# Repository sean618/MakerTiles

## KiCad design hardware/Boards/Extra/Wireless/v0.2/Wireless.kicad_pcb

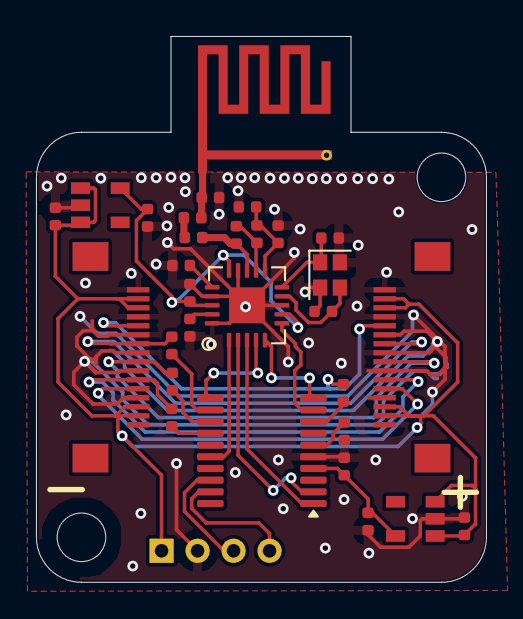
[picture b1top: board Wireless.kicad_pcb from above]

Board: 4 copper layers, 25.0 x 30.3 mm, 34 parts (0 on the bottom side), 31 nets.

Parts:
AE1: Antenna_MIFA_Cypress; Antenna_cypress_MIFA
C1: 0.1uF; C_0402_1005Metric
C2, C8, C9, C11, C12, C13: 4.7uF; C_0402_1005Metric
C3: 33nF; C_0402_1005Metric
C4: 2.2nF; C_0402_1005Metric
C5, C6: 12pF; C_0402_1005Metric
C7: 1pF; C_0402_1005Metric
C10: 1.5pF; C_0402_1005Metric
C14: 4.7pF; C_0402_1005Metric
H1, H2: M2.5MountingHole; MountingHole_2.7mm_M2.5_ISO7380
IGNORE1: Wireless v0.2; BoardText
J1, J3: FFC_connector_16p_hinge_lock
J4: swd_4pin; swd_header
L1: 8.2nH; C_0402_1005Metric
L3: 3.9nH; C_0402_1005Metric
L4: 2.7nH; C_0402_1005Metric
R1, R2, R3, R4: 120R; R_0402_1005Metric
R6: 22K; R_0402_1005Metric
U1, U2: ME6211C33M5G-N; SOT-23-5
U3: STM32G030F6P6; TSSOP-20_4.4x6.5mm_P0.65mm
U4: NRF24L01; QFN-20-1EP_4x4mm_P0.5mm_EP2.5x2.5mm
Y2: Crystal_16M_small; Crystal_SMD_2016-4Pin_2.0x1.6mm

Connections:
5V: C8.1, C11.1, J1.2, J1.3, J1.14, J1.15, J3.2, J3.3, J3.14, J3.15, J4.1, U1.1 (IN), U1.3 (EN), U2.1 (IN), U2.3 (EN)
GND: AE1.2 (GND), C1.2, C2.2, C3.2, C4.2, C5.2, C6.2, C7.2, C8.2, C9.2, C11.2, C12.2, C13.2, C14.2, J1.1, J1.4, J1.6, J1.8, J1.10, J1.13, J1.16, J3.1, J3.4, J3.7, J3.9, J3.11, J3.13, J3.16, J4.2, R6.1, U1.2 (GND), U2.2 (GND), U3.5 (VSS), U4.8 (VSS), U4.14 (VSS), U4.17 (VSS), U4.20 (VSS), U4.21 (VSS), Y2.2 (GND), Y2.4 (GND)
Interrupt/CAN: J1.12, J3.5
MISO: J1.9, J3.8, R4.2
MOSI: J1.11, J3.6, R2.2
unnamed: AE1.1 (A), C7.1, C10.2
unnamed: C10.1, L3.1
unnamed: C1.1, U3.6 (NRST)
unnamed: R1.1, U3.8 (PA1)
unnamed: R3.1, U3.12 (PA5)
unnamed: R4.1, U3.13 (PA6)
unnamed: R2.1, U3.14 (PA7)
unnamed: L1.1, L4.2, U4.12 (ANT1)
unnamed: L1.2, L3.2, U4.13 (ANT2)
unnamed: C3.1, U4.19 (DVDD)
unnamed: R6.2, U4.16 (IREF)
unnamed: C4.1, C14.1, L4.1, U4.11 (VDD_PA)
PS: J1.5, J3.12, R1.2
SCLK: J1.7, J3.10, R3.2
SWDCLK: J4.4, U3.19 (PA14/PA15)
SWDIO: J4.3, U3.18 (PA13)
VDD: C2.1, C12.1, U2.5 (OUT), U3.4 (VDD)
VDD_NRF: C9.1, C13.1, U1.5 (OUT), U4.7 (VDD), U4.15 (VDD), U4.18 (VDD)
W_CSN: U3.2 (PC14/PB9), U4.2 (CSN)
W_Enable: U3.16 (PA11/PA9), U4.1 (CE)
W_INT: U3.9 (PA2), U4.6 (IRQ)
W_MISO: U3.10 (PA3), U4.5 (MISO)
W_MOSI: U3.11 (PA4), U4.4 (MOSI)
W_SCK: U3.1 (PB7/PB8), U4.3 (SCK)
XC13: C5.1, U4.10 (XC1), Y2.1
XC23: C6.1, U4.9 (XC2), Y2.3

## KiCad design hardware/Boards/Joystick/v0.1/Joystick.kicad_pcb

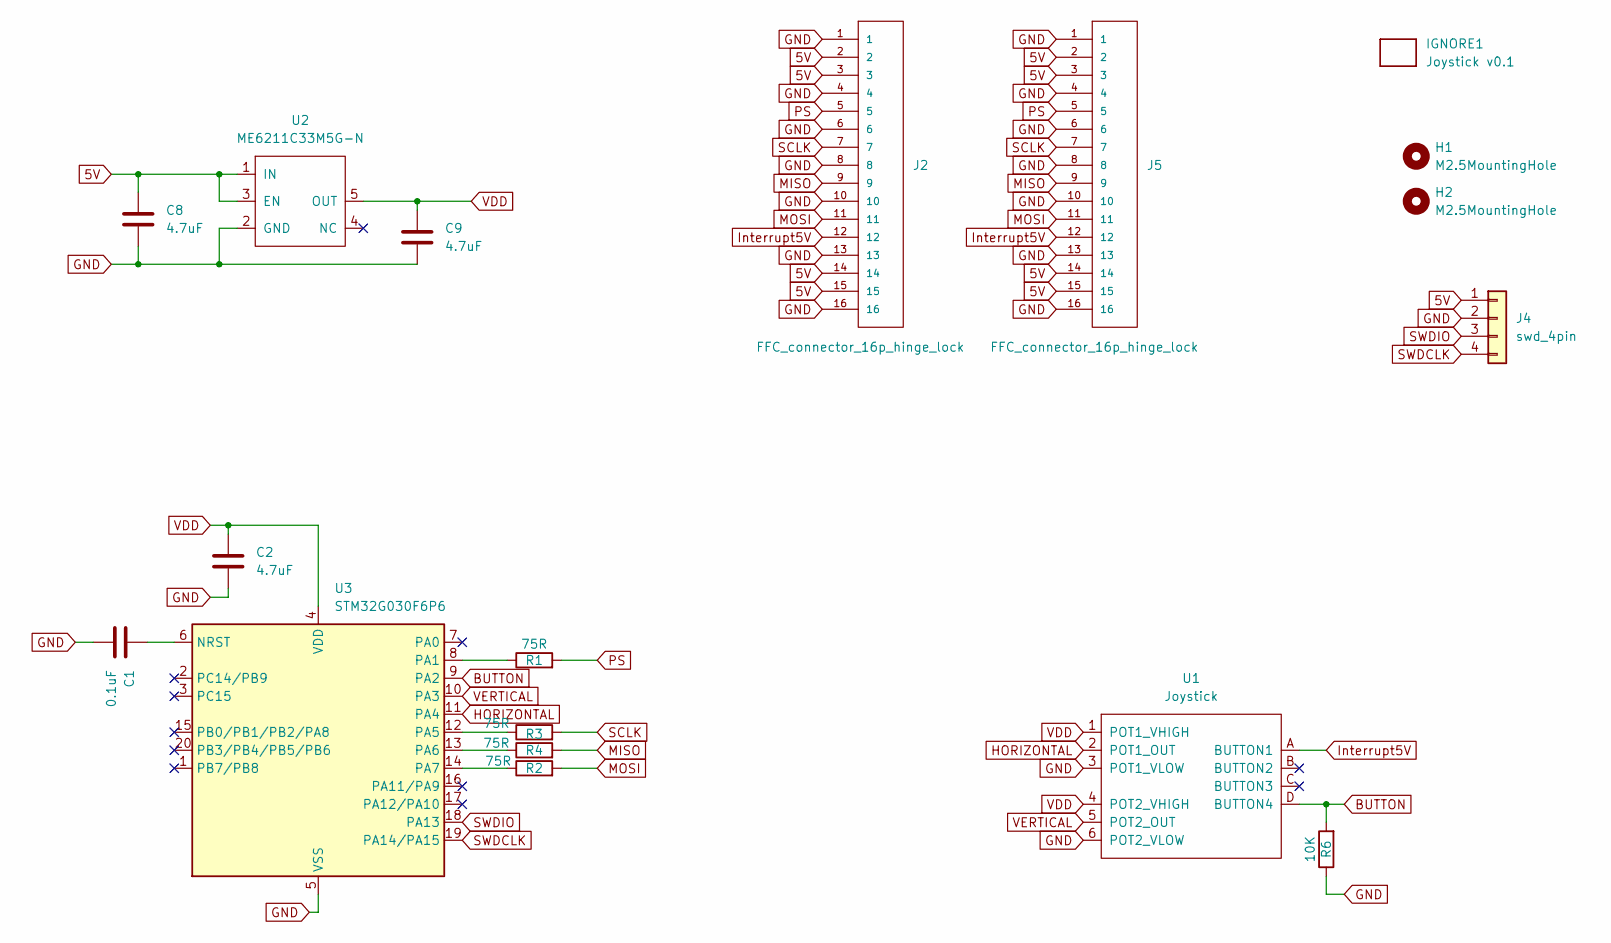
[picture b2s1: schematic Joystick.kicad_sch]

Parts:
C1: 0.1uF; C_0402_1005Metric
C2, C8, C9: 4.7uF; C_0402_1005Metric
H1, H2: M2.5MountingHole; MountingHole_2.7mm_M2.5_ISO7380
IGNORE1: Joystick v0.1; BoardText
J2, J5: FFC_connector_16p_hinge_lock
J4: swd_4pin; swd_header
R1, R2, R3, R4: 75R; R_0402_1005Metric
R6: 10K; R_0402_1005Metric
U1: Joystick
U2: ME6211C33M5G-N; SOT-23-5
U3: STM32G030F6P6; TSSOP-20_4.4x6.5mm_P0.65mm

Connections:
5V: C8.1, J2.2, J2.3, J2.14, J2.15, J4.1, J5.2, J5.3, J5.14, J5.15, U2.1 (IN), U2.3 (EN)
BUTTON: R6.2, U1.D (BUTTON4), U3.9 (PA2)
GND: C1.2, C2.2, C8.2, C9.2, J2.1, J2.4, J2.6, J2.8, J2.10, J2.13, J2.16, J4.2, J5.1, J5.4, J5.6, J5.8, J5.10, J5.13, J5.16, R6.1, U1.3 (POT1_VLOW), U1.6 (POT2_VLOW), U2.2 (GND), U3.5 (VSS)
HORIZONTAL: U1.2 (POT1_OUT), U3.11 (PA4)
Interrupt5V: J2.12, J5.12, U1.A (BUTTON1)
MISO: J2.9, J5.9, R4.2
MOSI: J2.11, J5.11, R2.2
unnamed: C1.1, U3.6 (NRST)
unnamed: R1.1, U3.8 (PA1)
unnamed: R3.1, U3.12 (PA5)
unnamed: R4.1, U3.13 (PA6)
unnamed: R2.1, U3.14 (PA7)
PS: J2.5, J5.5, R1.2
SCLK: J2.7, J5.7, R3.2
SWDCLK: J4.4, U3.19 (PA14/PA15)
SWDIO: J4.3, U3.18 (PA13)
VDD: C2.1, C9.1, U1.1 (POT1_VHIGH), U1.4 (POT2_VHIGH), U2.5 (OUT), U3.4 (VDD)
VERTICAL: U1.5 (POT2_OUT), U3.10 (PA3)

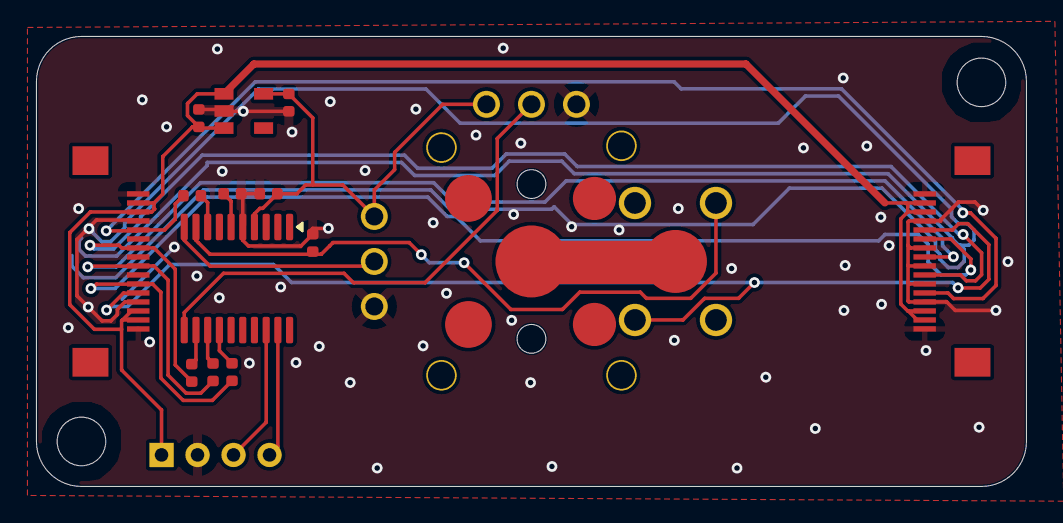
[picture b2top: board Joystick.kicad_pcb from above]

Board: 2 copper layers, 55.0 x 25.0 mm, 18 parts (0 on the bottom side), 18 nets.

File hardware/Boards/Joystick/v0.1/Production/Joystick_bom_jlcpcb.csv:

Comment,Designator,Footprint,LCSC Part Number
4.7uF,"C9,C8,C2",C_0402_1005Metric,C23733
Joystick,U1,Joystick,C146170
FFC_connector_16p_hinge_lock,"J5,J2",FFC_connector_16p_hinge_lock,C262665
ME6211C33M5G-N,U2,SOT-23-5,C81233
75R,"R2,R4,R1,R3",R_0402_1005Metric,C25133
STM32G030F6P6,U3,TSSOP-20_4.4x6.5mm_P0.65mm,C529330
10K,R6,R_0402_1005Metric,C25744
0.1uF,C1,C_0402_1005Metric,C1525

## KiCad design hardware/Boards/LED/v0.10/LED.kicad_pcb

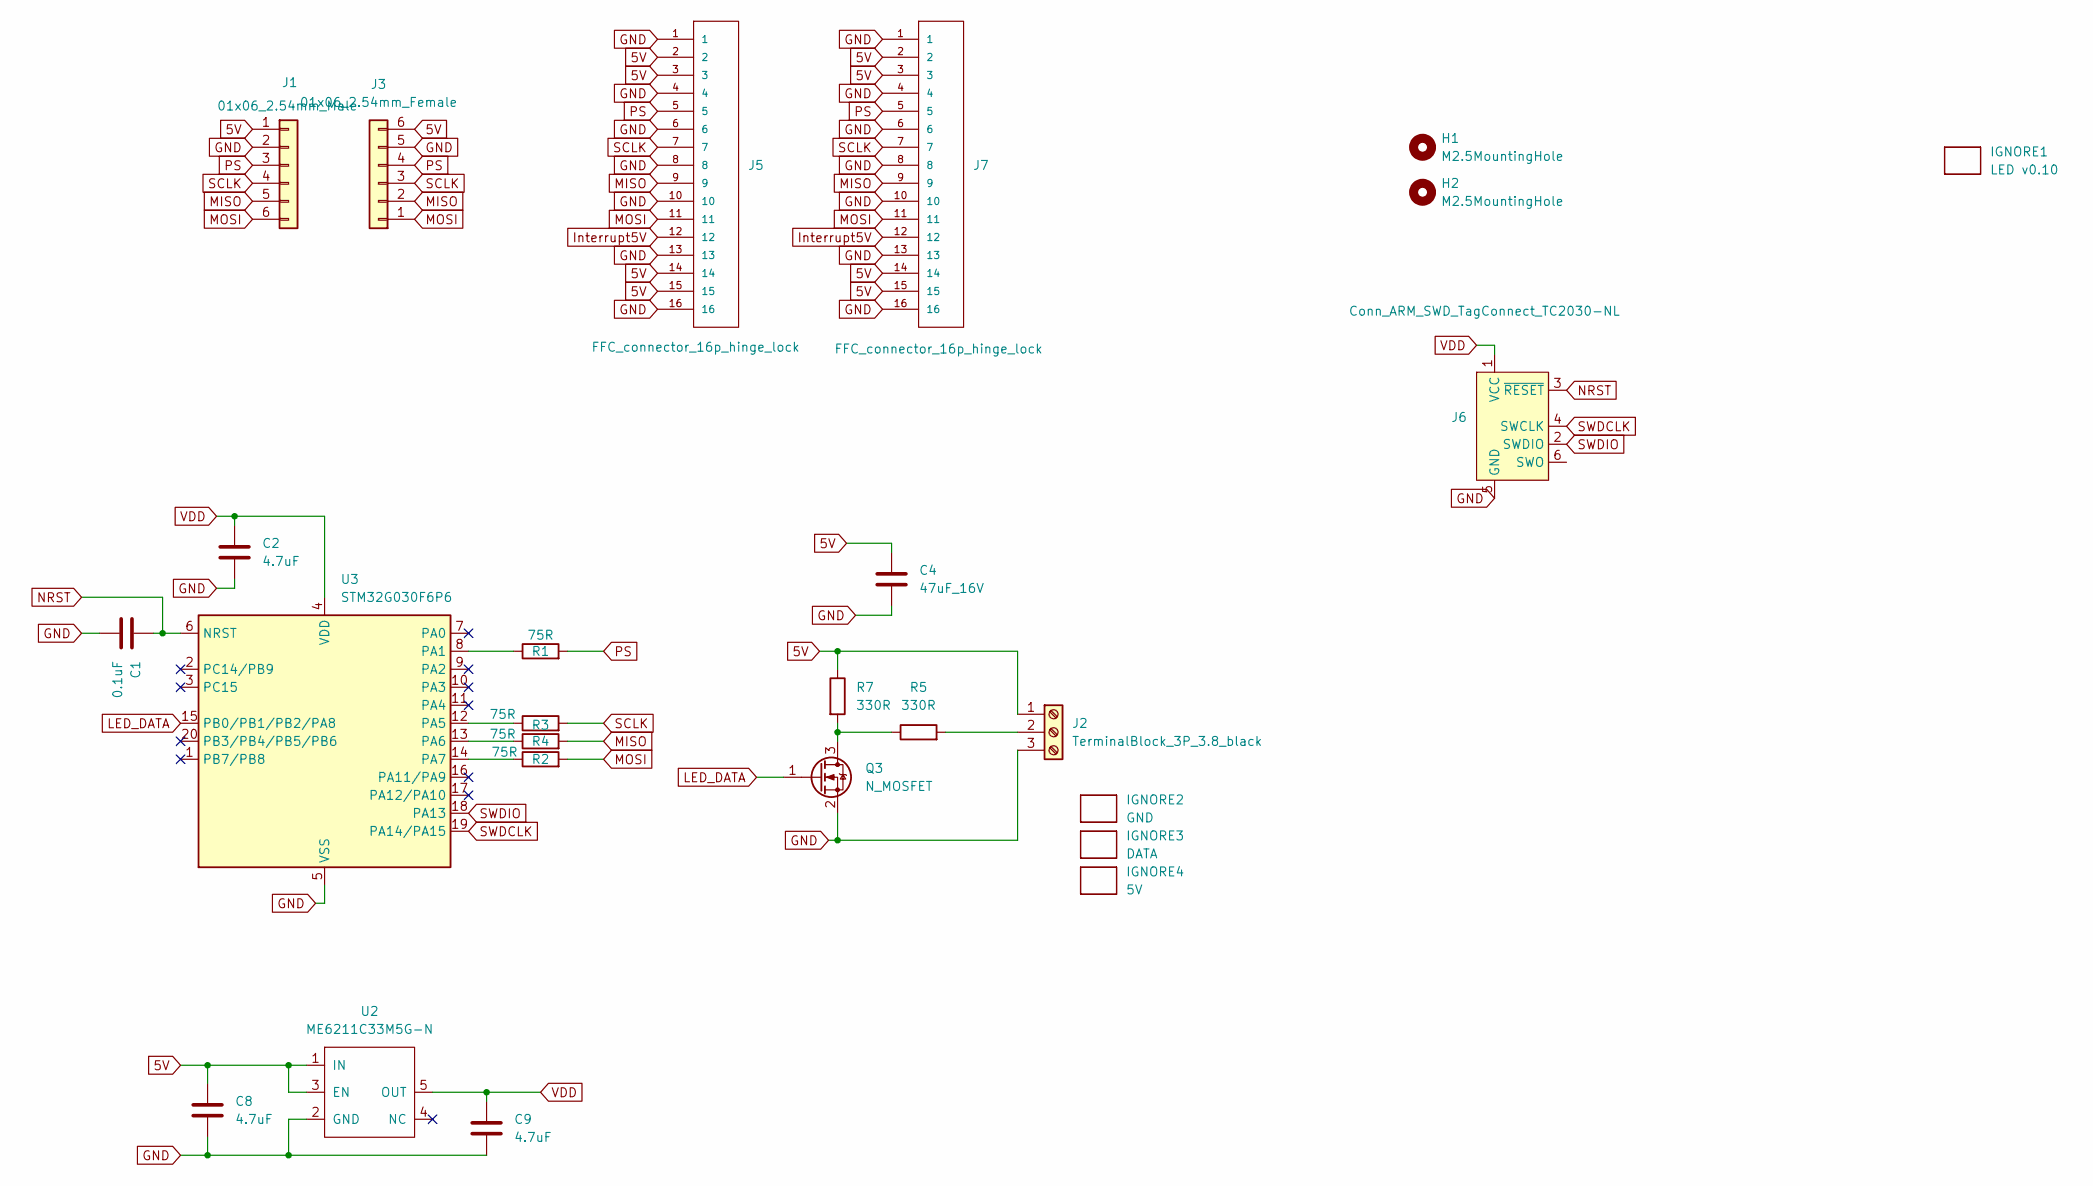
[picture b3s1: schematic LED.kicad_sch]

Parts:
C1: 0.1uF; C_0402_1005Metric
C2, C8, C9: 4.7uF; C_0402_1005Metric
C4: 47uF_16V; C_1210_3225Metric
H1, H2: M2.5MountingHole; MountingHole_2.7mm_M2.5_ISO7380
IGNORE1: LED v0.10; BoardText
IGNORE2: GND; BoardText
IGNORE3: DATA; BoardText
IGNORE4: 5V; BoardText
J1: 01x06_2.54mm_Male
J2: TerminalBlock_3P_3.8_black; TerminalBlock_03_P3.81mm_Horizontal
J3: 01x06_2.54mm_Female
J5, J7: FFC_connector_16p_hinge_lock
J6: Conn_ARM_SWD_TagConnect_TC2030-NL; Tag-Connect_TC2030-IDC-NL_2x03_P1.27mm_Vertical
Q3: N_MOSFET; SOT-23
R1, R2, R3, R4: 75R; R_0402_1005Metric
R5, R7: 330R; R_0402_1005Metric
U2: ME6211C33M5G-N; SOT-23-5
U3: STM32G030F6P6; TSSOP-20_4.4x6.5mm_P0.65mm

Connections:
5V: C4.1, C8.1, J1.1, J2.1, J3.6, J5.2, J5.3, J5.14, J5.15, J7.2, J7.3, J7.14, J7.15, R7.1, U2.1 (IN), U2.3 (EN)
GND: C1.2, C2.2, C4.2, C8.2, C9.2, J1.2, J2.3, J3.5, J5.1, J5.4, J5.6, J5.8, J5.10, J5.13, J5.16, J6.5 (GND), J7.1, J7.4, J7.6, J7.8, J7.10, J7.13, J7.16, Q3.2 (S), U2.2 (GND), U3.5 (VSS)
Interrupt5V: J5.12, J7.12
LED_DATA: Q3.1 (G), U3.15 (PB0/PB1/PB2/PA8)
MISO: J1.5, J3.2, J5.9, J7.9, R4.2
MOSI: J1.6, J3.1, J5.11, J7.11, R2.2
NRST: C1.1, J6.3 (~RESET), U3.6 (NRST)
unnamed: J2.2, R5.2
unnamed: Q3.3 (D), R5.1, R7.2
unnamed: R1.1, U3.8 (PA1)
unnamed: R3.1, U3.12 (PA5)
unnamed: R4.1, U3.13 (PA6)
unnamed: R2.1, U3.14 (PA7)
PS: J1.3, J3.4, J5.5, J7.5, R1.2
SCLK: J1.4, J3.3, J5.7, J7.7, R3.2
SWDCLK: J6.4 (SWCLK), U3.19 (PA14/PA15)
SWDIO: J6.2 (SWDIO), U3.18 (PA13)
VDD: C2.1, C9.1, J6.1 (VCC), U2.5 (OUT), U3.4 (VDD)

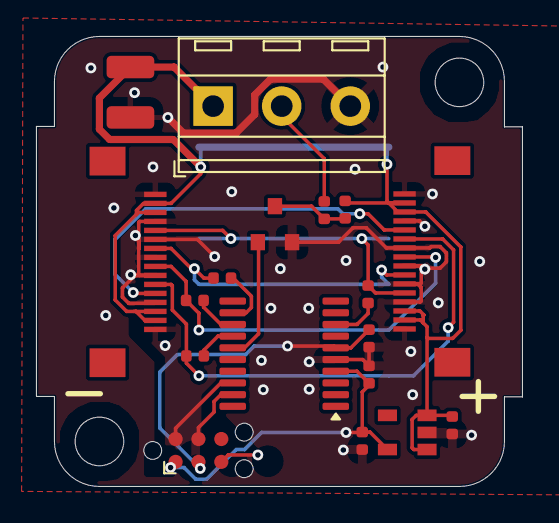
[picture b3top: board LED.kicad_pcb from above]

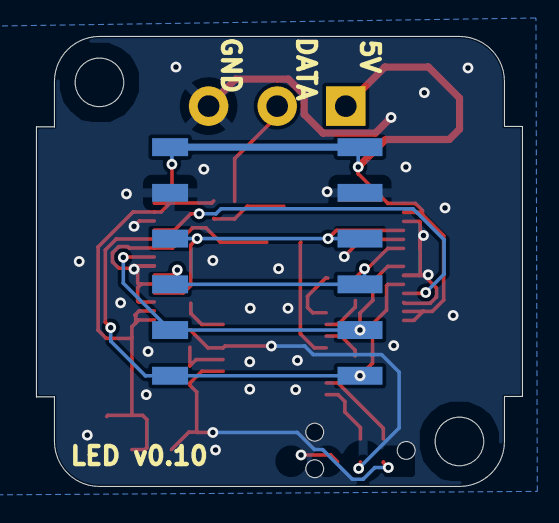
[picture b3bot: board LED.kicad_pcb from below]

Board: 4 copper layers, 27.0 x 25.0 mm, 26 parts (2 on the bottom side), 18 nets.

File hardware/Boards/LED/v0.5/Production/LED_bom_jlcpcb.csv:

Comment,Designator,Footprint,LCSC Part Number
4.7uF,"C9,C8,C2",C_0402_1005Metric,C23733
FFC_connector_16p_hinge_lock,"J7,J5",FFC_connector_16p_hinge_lock,C262665
47uF_16V,C4,C_1210_3225Metric,C77101
1K,"R5,R7",R_0402_1005Metric,C11702
ME6211C33M5G-N,U2,SOT-23-5,C81233
N_MOSFET,Q3,SOT-23,C8545
75R,"R2,R3,R4,R1",R_0402_1005Metric,C25133
STM32G030F6P6,U3,TSSOP-20_4.4x6.5mm_P0.65mm,C529330
TerminalBlock_3P_3.8_black,J2,TerminalBlock_03_P3.81mm_Horizontal,C881704
0.1uF,C1,C_0402_1005Metric,C1525
01x06_2.54mm_Male,J1,01x06_2.54mm_Male,C5242199
01x06_2.54mm_Female,J3,01x06_2.54mm_Female,C5142239
